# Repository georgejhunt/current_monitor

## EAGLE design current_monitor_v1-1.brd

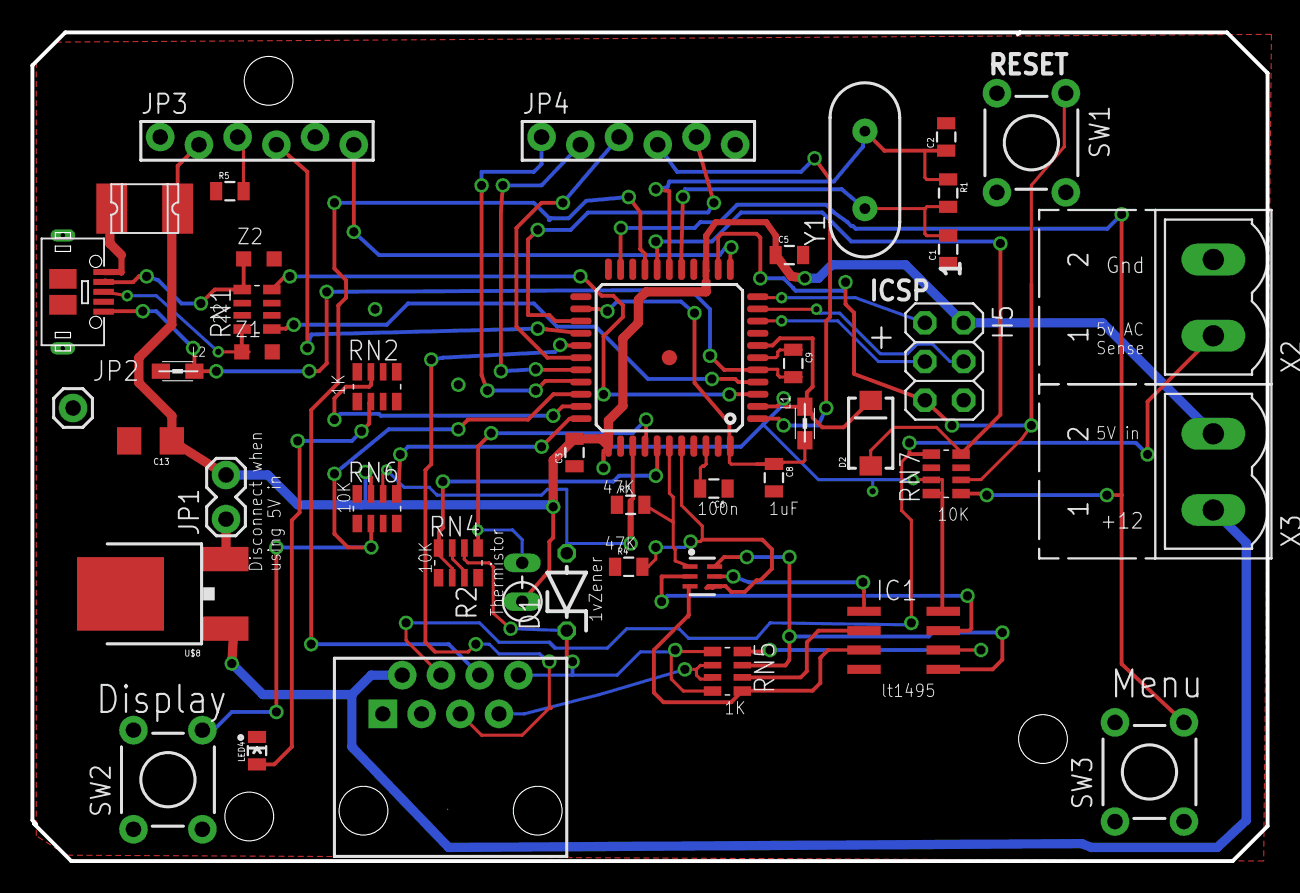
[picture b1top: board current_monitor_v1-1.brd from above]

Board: 2 copper layers, 81.0 x 54.4 mm, 44 parts (0 on the bottom side), 50 nets.

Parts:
C1, C2: 18p; 0805
C3, C5, C6: 100n; 0805
C8, C9: 1uF; 0805
C13: 22uF; 1206
D1: ZDIO-5
D2: SMA-DIODE
F1: 1812L
H5: ICSP; 2X03
IC1: LM4558D; SO08
JP1: 1X02_LOCK
JP2: M01PTH; 1X01
JP3, JP4: 1X06_FEMALE_LOCK.010
L1, L2: MH2029-300Y; 0805
LED4: ON Green; LED0805
R1: 1M; 0805
R2: THERMISTOR-2,5; RS-2,5
R4, R7: 47k; 0805
R5: 2.2K; 0805
RN1: 22; CRA06S
RN2: 1k; CRA06S
RN4, RN6, RN7: 10k; CRA06S
RN5: 1K; CRA06S
SW1: RESET; TACTILE-PTH
SW2, SW3: Display; TACTILE-PTH
U1: ATMEGA32U4-XUAU; TQFP44-PAD
U$5: MMDT3904; SOT363
U$6: RJ45-8PTH; RJ45-8
U$8: LM2931_FIXED; DPAK
U$12: USB-MICRO-B-UNIVERSAL
X2, X3: MSTBV2
Y1: 16MHz; HC49US
Z1, Z2: CG0603MLC-05E; CT/CN0603

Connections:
12V: U$6.2, U$8.1, X3.1
+5V: C3.2, C5.1, C13.1, D2.C, F1.P$2, H5.2, IC1.8, JP1.2, JP3.2, L1.1, R2.1, RN6.7, RN7.7, RN7.8, U1.2, U1.7, U1.14, U1.34, X3.2
A0: D1.A, RN6.6, U1.36
A1: R2.2, RN4.5, U1.37
A2: RN4.2, RN4.8, U1.38
A3: R7.2, U1.39, U$5.1
A4: R4.2, U1.40, U$5.4
AC_SENSE: RN7.5, U$6.4, X2.1
AREF: C6.2, U1.42
AVCC: C8.1, L1.2, U1.24, U1.44
D1/TX: RN7.1, SW3.4, U1.21
D2/SDA: U1.19, U$6.6
D3/SCL: D2.A, RN7.4, U1.18
D4: JP4.5, U1.25
D5*: RN6.2, SW2.4, U1.31
D6*: U1.27, U$6.5
D7: JP4.4, U1.1
D_M: RN1.5, U$12.D-, Z2.1
D_P: RN1.8, U$12.D+, Z1.1
GND: C1.1, C2.2, C3.1, C5.2, C6.1, C8.2, C13.2, H5.6, IC1.4, JP3.1, JP3.5, JP4.6, L2.2, LED4.C, R4.1, R5.1, R7.1, RN4.1, RN4.4, RN6.3, RN6.4, SW1.4, SW2.2, SW3.2, U1.15, U1.23, U1.35, U1.43, U$6.1, U$6.3, U$8.4, X2.2, Z1.2, Z2.2
HWB: RN6.5, U1.33
IO8: JP4.3, U1.28
IO9*: JP4.2, U1.29
IO10*: JP4.1, U1.30
IO11*: JP3.6, U1.12
IO12: JP3.4, U1.26
IO13*: RN2.7, U1.32
LED4_ANODE: LED4.A, RN2.2
MISO: H5.1, U1.11
MOSI: H5.4, U1.10
unnamed: IC1.5, RN5.7, U$5.6
unnamed: IC1.2, RN5.6
unnamed: IC1.6, RN5.8
unnamed: IC1.1, U$5.5
unnamed: IC1.7, U$5.2
unnamed: IC1.3, RN5.5, U$5.3
unnamed: F1.P$1, U$12.VCC
unnamed: JP1.1, U$8.3
unnamed: RN4.3, RN4.7
unnamed: JP3.3, R5.2
RD_M: RN1.4, U1.3
RD_P: RN1.1, U1.4
RESET: H5.5, RN7.2, SW1.1, U1.13
SCK: H5.3, U1.9
SHUNT-MINUS: D1.C, RN4.6, RN5.1, RN5.4, U$6.8
SHUNT-PLUS: RN5.2, RN5.3, U$6.7
UCAP: C9.1, U1.6
UGND: C9.2, L2.1, U1.5, U$12.GND
XTAL1: C2.1, R1.1, U1.17, Y1.2
XTAL2: C1.2, R1.2, U1.16, Y1.1

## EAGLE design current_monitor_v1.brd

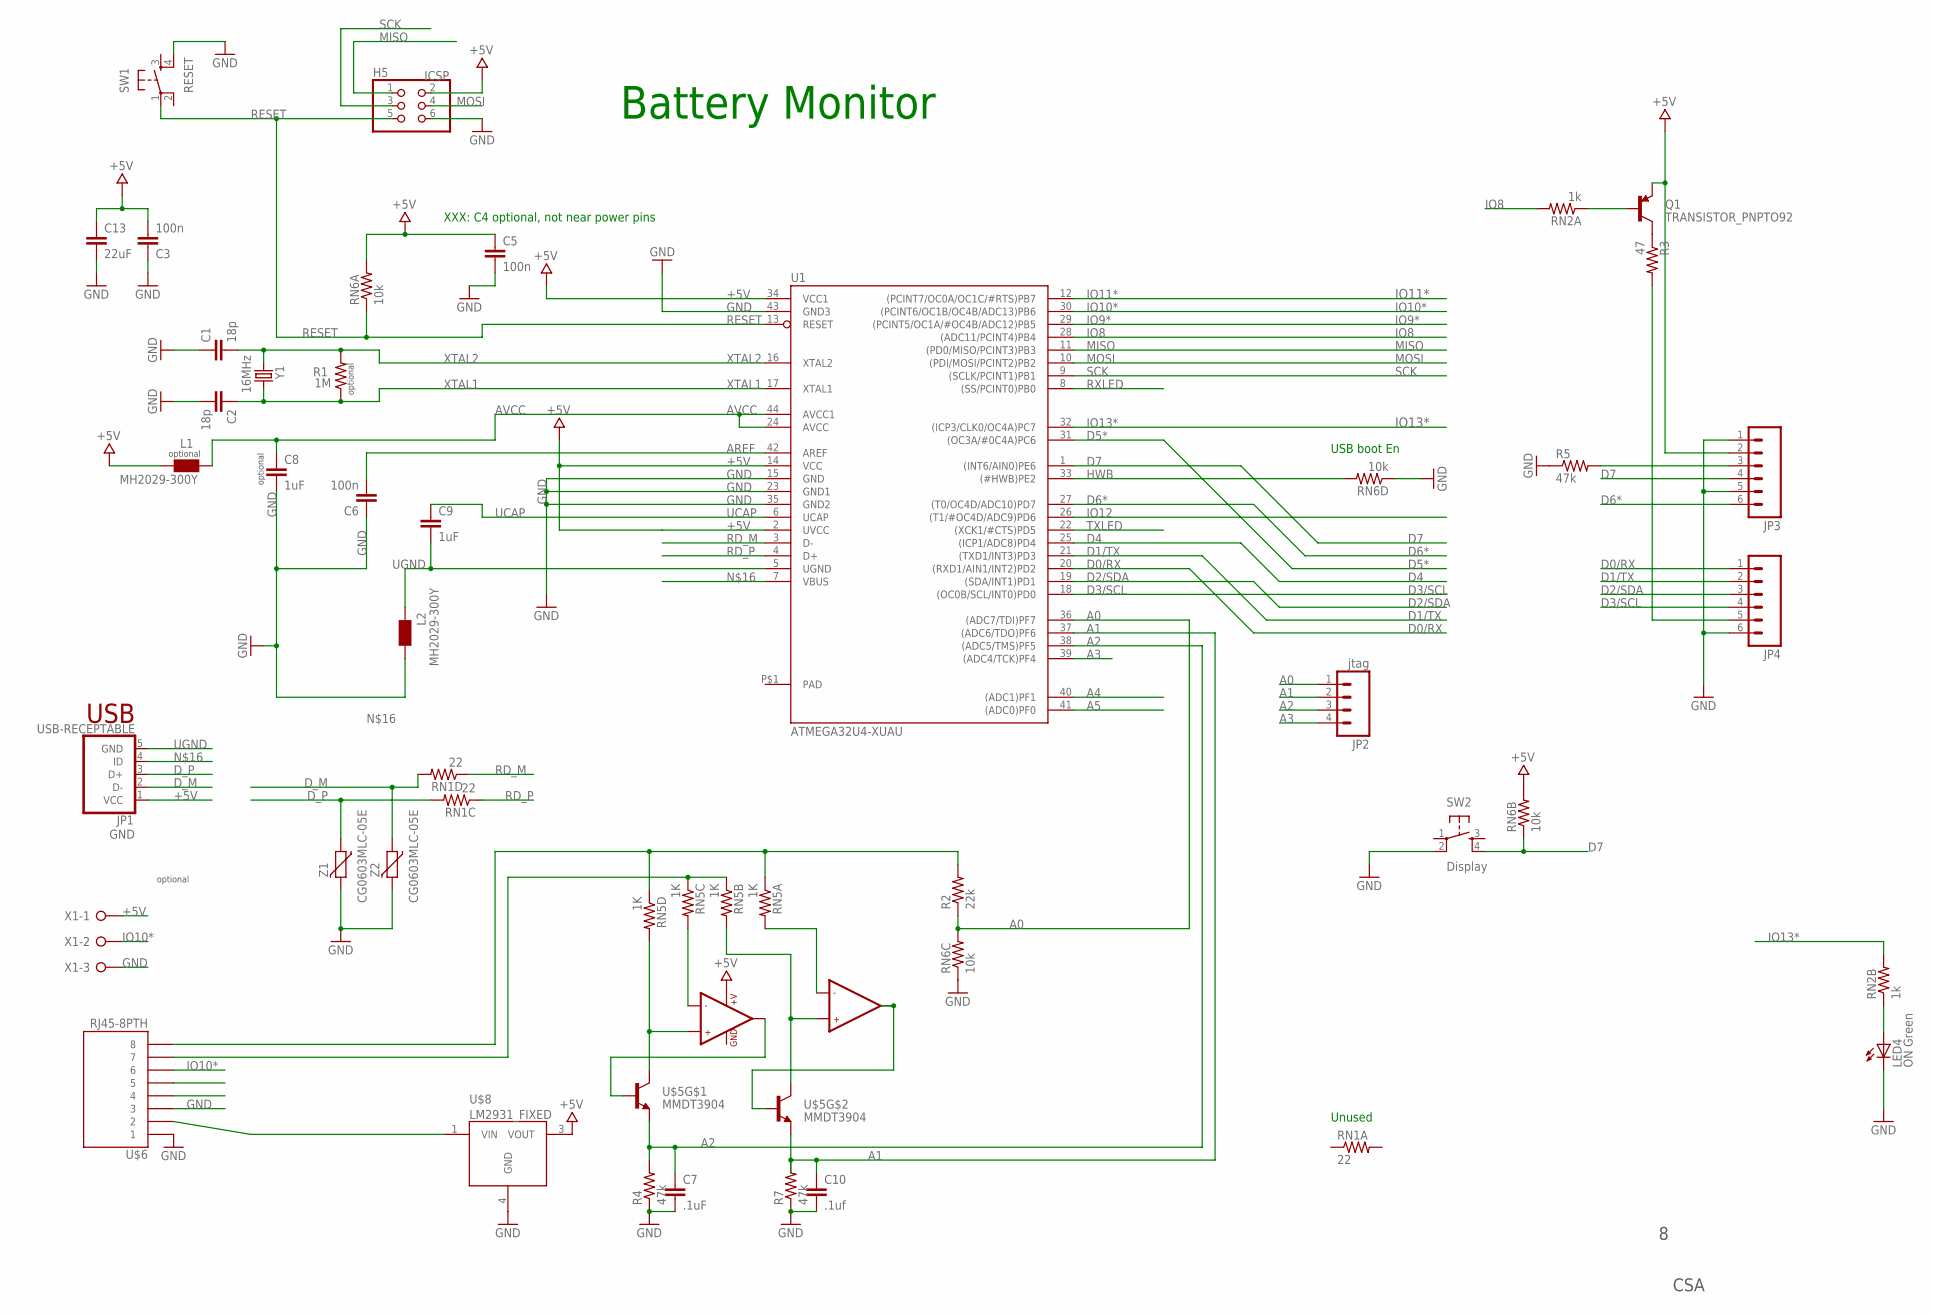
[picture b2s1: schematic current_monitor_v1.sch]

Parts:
C1, C2: 18p; 0805
C3, C5, C6: 100n; 0805
C7: .1uF; 0805
C8, C9: 1uF; 0805
C10: .1uf; 0805
C13: 22uF; 1206
H5: ICSP; 2X03
JP1: USB-RECEPTABLE; FCI-10103594-0001LF
JP2: jtag; 1X04_LOCK
JP3, JP4: M06POGOPIN_HOLES_ONLY; 1X06_HOLES_ONLY
L1, L2: MH2029-300Y; 0805
LED4: ON Green; LED0805
Q1: TRANSISTOR_PNPTO92; TO-92
R1: 1M; 0805
R2: 22k; 0805
R3: 47; 0207/15
R4, R5, R7: 47k; 0805
RN1: 22; CRA06S
RN2: 1k; CRA06S
RN5: 1K; CRA06S
RN6: 10k; CRA06S
SW1: RESET; TACTILE-PTH
SW2: Display; TACTILE-PTH
U1: ATMEGA32U4-XUAU; TQFP44-PAD
U$2: LMV358; SO08
U$5: MMDT3904; SOT363
U$6: RJ45-8PTH; RJ45-8
U$8: LM2931_FIXED; DPAK
X1: W237-03P; W237-133
Y1: 16MHz; HC49US
Z1, Z2: CG0603MLC-05E; CT/CN0603

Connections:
+5V: C3.2, C5.1, C13.1, H5.2, JP1.1 (VCC), JP3.2, L1.1, Q1.1 (E), RN6.7 (2), RN6.8 (2), U1.2 (UVCC), U1.14 (VCC), U1.34 (VCC1), U$2.8 (+V), U$8.3 (VOUT), X1.1
A0: JP2.1, R2.1, RN6.6 (2), U1.36 ((ADC7/TDI)PF7)
A1: C10.1, JP2.2, R7.2, U1.37 ((ADC6/TDO)PF6), U$5.1 (E)
A2: C7.1, JP2.3, R4.2, U1.38 ((ADC5/TMS)PF5), U$5.4 (E)
A3: JP2.4, U1.39 ((ADC4/TCK)PF4)
A4: U1.40 ((ADC1)PF1)
A5: U1.41 ((ADC0)PF0)
AREF: C6.2, U1.42 (AREF)
AVCC: C8.1, L1.2, U1.24 (AVCC), U1.44 (AVCC1)
D0/RX: JP4.1, U1.20 ((RXD1/AIN1/INT2)PD2)
D1/TX: JP4.2, U1.21 ((TXD1/INT3)PD3)
D2/SDA: JP4.3, U1.19 ((SDA/INT1)PD1)
D3/SCL: JP4.4, U1.18 ((OC0B/SCL/INT0)PD0)
D4: U1.25 ((ICP1/ADC8)PD4)
D5*: U1.31 ((OC3A/#0C4A)PC6)
D6*: JP3.6, U1.27 ((T0/OC4D/ADC10)PD7)
D7: JP3.4, RN6.2 (1), SW2.4, U1.1 ((INT6/AIN0)PE6)
D_M: JP1.2 (D-), RN1.5 (2), Z2.1
D_P: JP1.3 (D+), RN1.6 (2), Z1.1
GND: C1.1, C2.2, C3.1, C5.2, C6.1, C7.2, C8.2, C10.2, C13.2, H5.6, JP3.1, JP3.5, JP4.6, L2.2, LED4.C, R4.1, R5.1, R7.1, RN6.3 (1), RN6.4 (1), SW1.4, SW2.2, U1.15 (GND), U1.23 (GND1), U1.35 (GND2), U1.43 (GND3), U$2.4 (GND), U$6.1, U$6.3, U$8.4 (GND), X1.3, Z1.2, Z2.2
HWB: RN6.5 (2), U1.33 ((#HWB)PE2)
IO8: RN2.8 (2), U1.28 ((ADC11/PCINT4)PB4)
IO9*: U1.29 ((PCINT5/OC1A/#OC4B/ADC12)PB5)
IO10*: U1.30 ((PCINT6/OC1B/OC4B/ADC13)PB6), U$6.6, X1.2
IO11*: U1.12 ((PCINT7/OC0A/OC1C/#RTS)PB7)
IO12: U1.26 ((T1/#OC4D/ADC9)PD6)
IO13*: RN2.7 (2), U1.32 ((ICP3/CLK0/OC4A)PC7)
LED4_ANODE: LED4.A, RN2.2 (1)
MISO: H5.1, U1.11 ((PD0/MISO/PCINT3)PB3)
MOSI: H5.4, U1.10 ((PDI/MOSI/PCINT2)PB2)
unnamed: RN5.5 (2), U$2.3 (+IN1), U$5.3 (C)
unnamed: RN5.8 (2), U$2.6 (-IN2)
unnamed: RN5.7 (2), U$2.5 (+IN2), U$5.6 (C)
unnamed: U$2.1 (OUT1), U$5.5 (B)
unnamed: U$2.7 (OUT2), U$5.2 (B)
unnamed: RN5.6 (2), U$2.2 (-IN1)
unnamed: R2.2, RN5.1, RN5.4 (1), U$6.8
unnamed: RN5.2 (1), RN5.3 (1), U$6.7
unnamed: Q1.3 (C), R3.1
unnamed: JP3.3, R5.2
unnamed: JP4.5, R3.2
unnamed: JP1.4 (ID), U1.7 (VBUS)
unnamed: U$6.2, U$8.1 (VIN)
unnamed: Q1.2 (B), RN2.1
PAD: U1.P$1 (PAD)
RD_M: RN1.4 (1), U1.3 (D-)
RD_P: RN1.3 (1), U1.4 (D+)
RESET: H5.5, RN6.1, SW1.1, U1.13 (RESET)
RXLED: U1.8 ((SS/PCINT0)PB0)
SCK: H5.3, U1.9 ((SCLK/PCINT1)PB1)
TXLED: U1.22 ((XCK1/#CTS)PD5)
UCAP: C9.1, U1.6 (UCAP)
UGND: C9.2, JP1.5 (GND), L2.1, U1.5 (UGND)
XTAL1: C2.1, R1.1, U1.17 (XTAL1), Y1.2
XTAL2: C1.2, R1.2, U1.16 (XTAL2), Y1.1

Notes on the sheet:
Battery Monitor
USB boot En
USB
optional
CSA
Unused
XXX: C4 optional, not near power pins

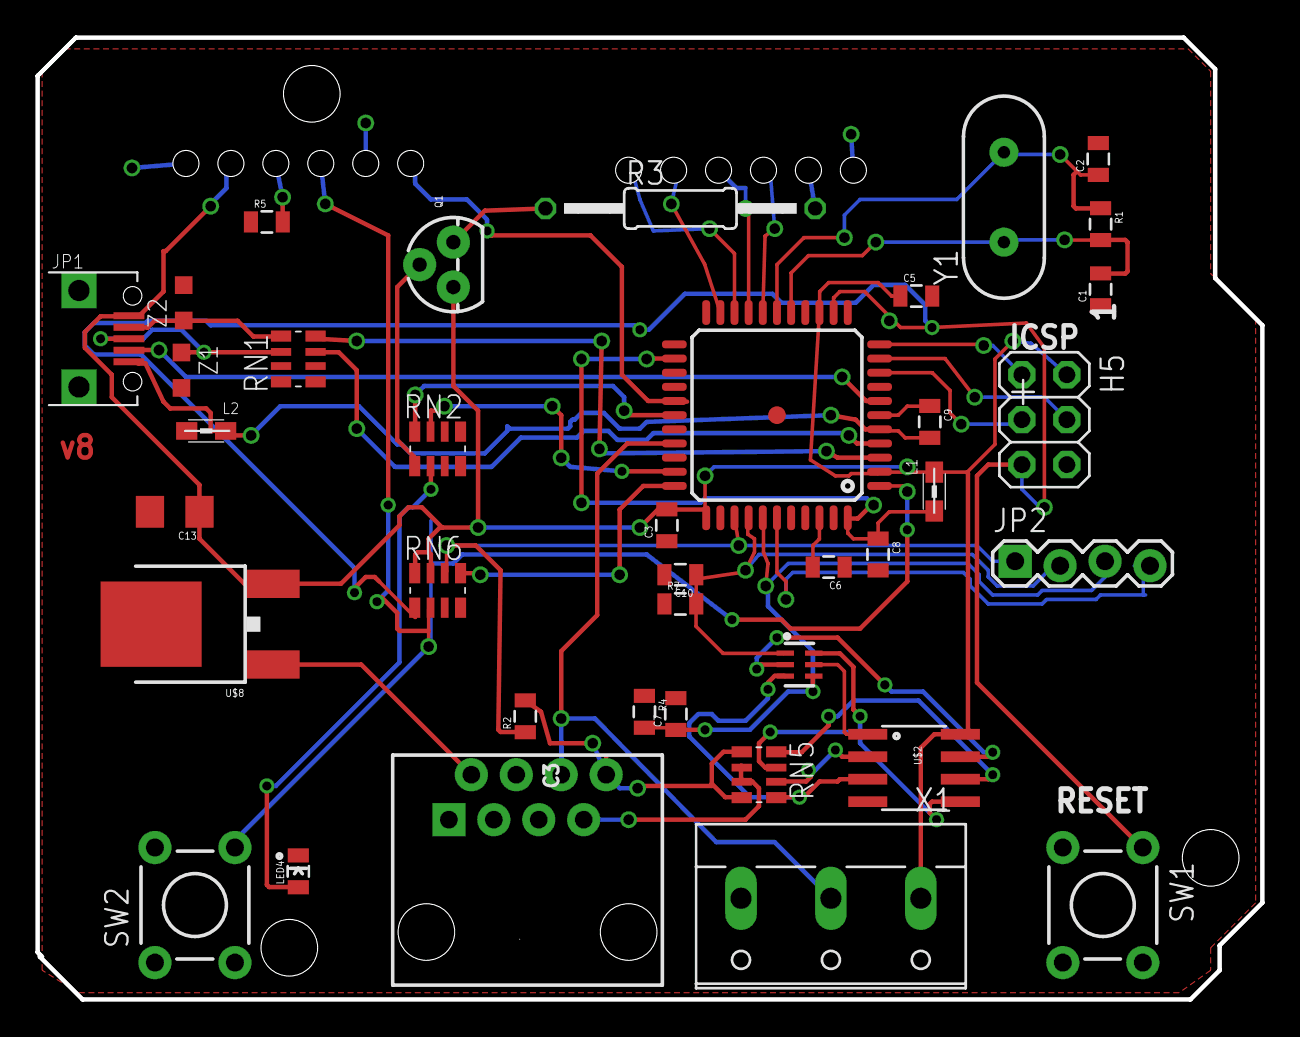
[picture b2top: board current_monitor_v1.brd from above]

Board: 2 copper layers, 69.2 x 54.4 mm, 40 parts (0 on the bottom side), 45 nets.

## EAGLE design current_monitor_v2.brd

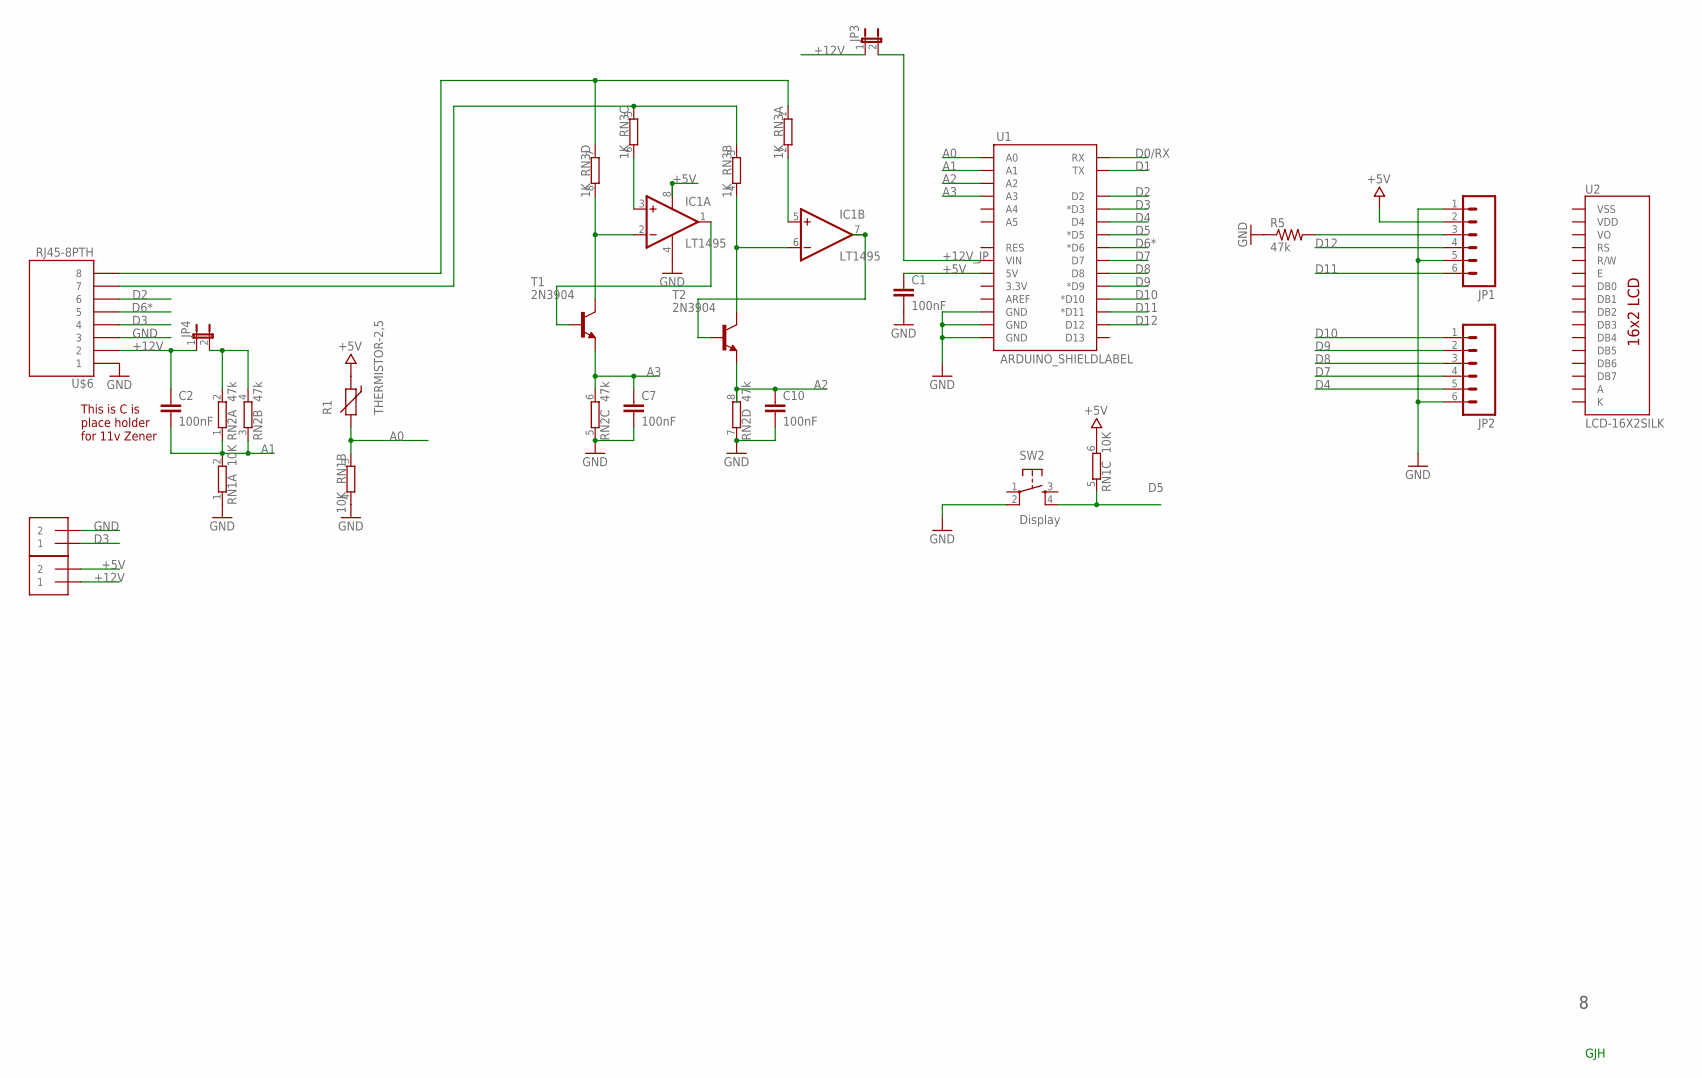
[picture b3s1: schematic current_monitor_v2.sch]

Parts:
C1, C2, C7, C10: 100nF; CAP-PTH-5MM
IC1: LT1495; SOCKED-08
J1, J2: 1X2-3.5MM
JP1, JP2: M06FEMALE_LOCK; 1X06_FEMALE_LOCK.010
JP3, JP4: JUMPER-2PTH; 1X02
R1: THERMISTOR-2,5; RS-2,5
R5: 47k; AXIAL-0.3
RN1: 10K; SIL6
RN2: 47k; SIL8
RN3: 1K; SIL8
SW2: Display; TACTILE-PTH
T1, T2: 2N3904; TO92-EBC-OVAL
U1: ARDUINO_SHIELDLABEL; DUEMILANOVE_SHIELD
U2: LCD-16X2SILK; LCD-16X2
U$6: RJ45-8PTH; RJ45-8

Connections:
+5V: C1.1, IC1.8 (V+), J2.2, JP1.2, R1.1, RN1.6 (2), U1.5V
+12V: C2.1, J2.1, JP3.1, JP4.1, U$6.2
+12V_JP: JP3.2, U1.VIN
+12V_JP2: JP4.2, RN2.2, RN2.4 (2)
A: U2.15 (A)
A0: R1.2, RN1.3 (1), U1.A0
A1: C2.2, RN1.2, RN2.1, RN2.3 (1), U1.A1
A2: C10.1, RN2.8 (2), T2.E, U1.A2
A3: C7.1, RN2.6 (2), T1.E, U1.A3
D0/RX: U1.RX
D1: U1.TX
D2: U1.D2, U$6.6
D3: J1.1, U1.D3 (*D3), U$6.4
D4: JP2.5, U1.D4
D5: RN1.5 (1), SW2.4, U1.D5 (*D5)
D6*: U1.D6 (*D6), U$6.5
D7: JP2.4, U1.D7
D8: JP2.3, U1.D8
D9: JP2.2, U1.D9 (*D9)
D10: JP2.1, U1.D10 (*D10)
D11: JP1.6, U1.D11 (*D11)
D12: JP1.4, U1.D12
GND: C1.2, C7.2, C10.2, IC1.4 (V-), J1.2, JP1.1, JP1.5, JP2.6, R5.P$1 (1), RN1.1, RN1.4 (2), RN2.5 (1), RN2.7 (1), SW2.2, U1.GND@0 (GND), U1.GND@1 (GND), U1.GND@2 (GND), U$6.1, U$6.3
K: U2.16 (K)
unnamed: IC1.2 (-IN), RN3.8 (2), T1.C
unnamed: IC1.5 (+IN), RN3.2
unnamed: IC1.6 (-IN), RN3.4 (2), T2.C
unnamed: IC1.1 (OUT), T1.B
unnamed: IC1.7 (OUT), T2.B
unnamed: IC1.3 (+IN), RN3.6 (2)
unnamed: RN3.1, RN3.7 (1), U$6.8
unnamed: RN3.3 (1), RN3.5 (1), U$6.7
unnamed: JP1.3, R5.P$2 (2)
VDD: U2.2 (VDD)
VSS: U2.1 (VSS)

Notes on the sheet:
GJH
This is C is place holder for 11v Zener

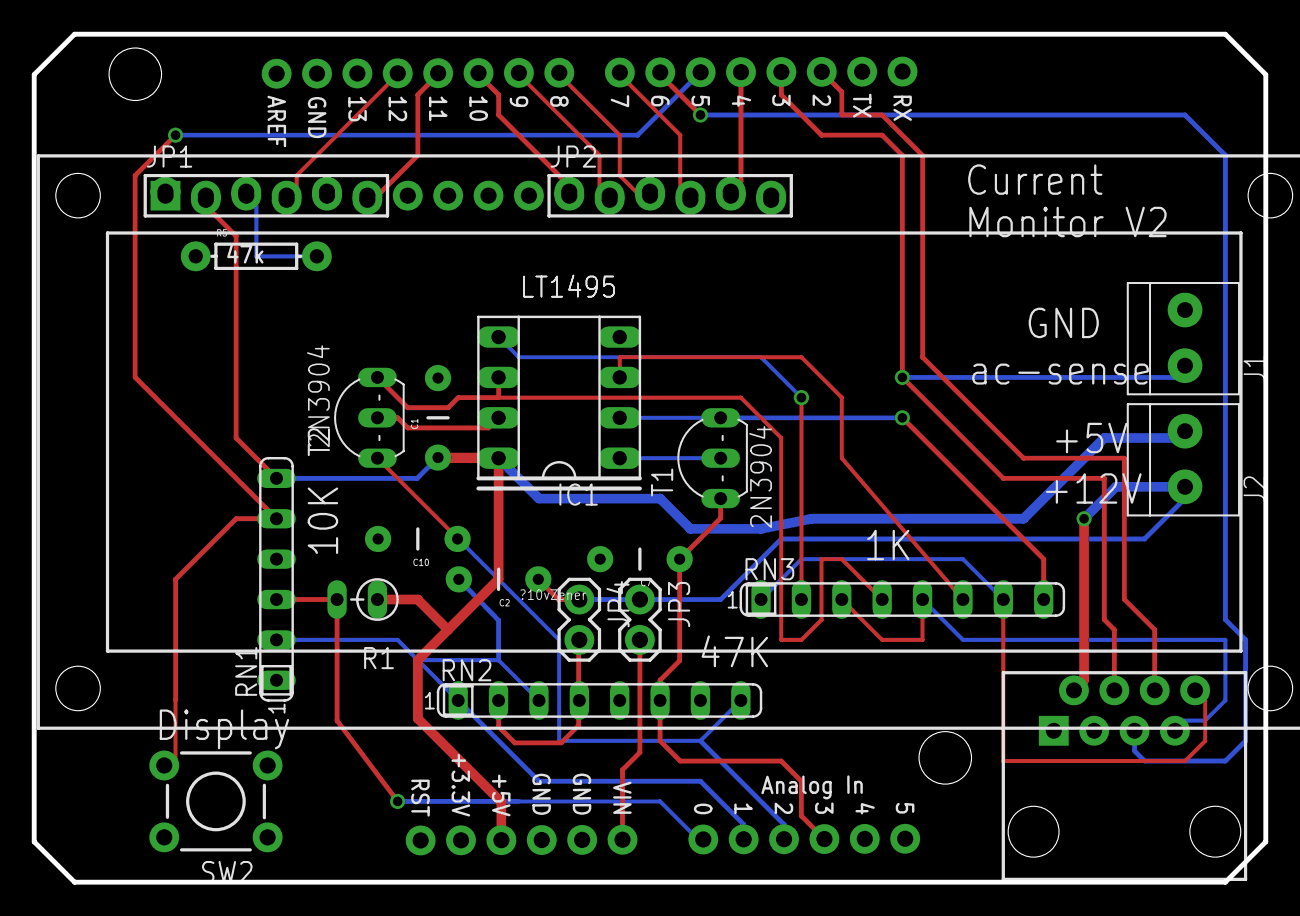
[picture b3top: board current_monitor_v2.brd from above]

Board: 2 copper layers, 77.5 x 53.3 mm, 22 parts (0 on the bottom side), 29 nets.

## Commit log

2014-01-10 all of second page deleted
2014-01-11 most of un-needed items removed. Current sense mostly in place
2014-01-11 didn't select brd and sch together -- goes with last commit
2014-01-11 starting to eliminate vias, work with component orientation
2014-01-12 changed usb connector, most of the devices are connected
2014-01-12 added terminal block to sense power on
2014-01-14 some hand routing, currently about4 air wires
2014-02-15 as submitted to osh park fab house
2014-04-06 start tracking surface mount board -- hand layout
2014-04-09 changed v1.1 to v1-1 to please git, surface mount board ready to submit to osh park
2014-11-03 submitted to fab 11/3/14 -- fixed agnd and usb drill sizes

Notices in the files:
parts and their libraries:
SparkFun-Electromechanical: Licensing: CC v3.0 Share-Alike You are welcome to use this library for commercial purposes.
